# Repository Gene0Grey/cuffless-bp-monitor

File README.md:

# Cuffless BP Monitor

Cuffless, non-invasive blood-pressure monitoring using **Pulse Transit Time (PTT)**: one
AD8232 ECG gives the timing reference (the R-peak), and four MAX30102 PPG sensors on a
TCA9548A I²C multiplexer pick up the pulse wave at fingertips and earlobes. An ESP32
samples everything, filters it, and streams the waveforms.

This repository holds the carrier PCB (KiCad 9), the ESP32 firmware, and the
[project report](docs/Cuffless_BP_Monitor_Report.docx).

> **Not a medical device.** For research and education only; not validated for clinical use.

## How it works

Each heartbeat shows up as an R-peak on the ECG (t = 0). The pressure pulse it launches
reaches a peripheral site a short time later, where a PPG sensor sees it. That delay is the
PTT. Higher blood pressure stiffens the arteries, the pulse travels faster, and PTT gets
shorter:

```
BP ≈ a · (1 / PTT²) + b
```

`a` and `b` are fitted per person against a reference cuff. Using a proximal site
(earlobe, short PTT) and distal sites (fingertips, longer PTT) gives several transit times
per beat, for cross-checking and rejecting motion artefacts.

## System overview

The ECG is analog, so it goes straight to an ADC1 pin and keeps working with Wi-Fi on.
All four MAX30102 sensors share I²C address 0x57, so the TCA9548A connects one at a time.

## Hardware

### Carrier board

| | |
|---|---|
| Size | 95.5 × 76 mm, 4 × M3 holes |
| Copper | Single-sided (bottom), through-hole only, no vias. Built to be etched at home |
| Tracks | 0.5 mm signal, 0.8 mm power, ≥ 0.6 mm clearance, ground pour |
| Pads | 1.9 mm pads on 1.0 mm holes, sized for a hand drill |
| Power in | USB on the ESP32, or J1 (JST-PH 2-pin) → ESP32 VIN |

The four PPG sockets sit in one straight row, PPG1–PPG4 left to right on mux channels 0–3.
The bottom copper, seen from the component side:

### Renders

<table>
  <tr>
    <td></td>
    <td></td>
  </tr>
  <tr>
    <td align="center">Assembled, front right</td>
    <td align="center">Assembled, from the back: USB, 5V IN and the ECG jack</td>
  </tr>
  <tr>
    <td colspan="2"></td>
  </tr>
  <tr>
    <td colspan="2" align="center">The four PPG sockets, PPG1&ndash;PPG4 on mux channels 0&ndash;3</td>
  </tr>
  <tr>
    <td></td>
    <td></td>
  </tr>
  <tr>
    <td align="center">Bare board, top: silkscreen and pin names</td>
    <td align="center">Bare board, bottom: the single copper layer</td>
  </tr>
</table>

### Parts

| Ref | Part | Qty | Purpose |
|---|---|---|---|
| U1 | ESP32 DevKit V1, 30-pin (CP2102) | 1 | Acquisition, DSP, telemetry |
| U2 | TCA9548A I²C mux module (HW-617) | 1 | Addresses the four identical sensors |
| U3–U6 | MAX30102 module (MH-ET LIVE) | 4 | PPG: 2 fingers, 2 earlobes |
| U7 | SparkFun AD8232 (SEN-12650) + electrodes | 1 | ECG / R-peak reference |
| J1 | JST-PH 2-pin, vertical | 1 | 5 V input |
| C1 | 10 µF electrolytic | 1 | 3V3 bulk decoupling |
| JP1–JP5 | Bare-wire links | 5 | Jumpers for the single copper layer |

For portable use: a 3.7 V LiPo (1250 mAh) and an XL6009 boost converter set to 5.0 V, with
470 µF + 0.1 µF across both its input and its output. Full list:
[`hardware/docs/bom.csv`](hardware/docs/bom.csv).

### Pin map

| Module pin | ESP32 |
|---|---|
| TCA9548A VIN / GND | 3V3 / GND |
| TCA9548A SDA / SCL | GPIO21 / GPIO22 |
| TCA9548A A0, A1, A2 | GND (address 0x70) |
| TCA9548A RST | 3V3 (through link JP5) |
| MAX30102 #1 (finger) SDA / SCL | mux SD0 / SC0 |
| MAX30102 #2 (finger) SDA / SCL | mux SD1 / SC1 |
| MAX30102 #3 (earlobe) SDA / SCL | mux SD2 / SC2 |
| MAX30102 #4 (earlobe) SDA / SCL | mux SD3 / SC3 |
| AD8232 OUTPUT | GPIO34 (ADC1, works with Wi-Fi on) |
| AD8232 LO+ / LO− | GPIO32 / GPIO33 |
| AD8232 3.3V / GND | 3V3 / GND |
| AD8232 SDN, MAX30102 INT / RD / IRD | not connected |

All MAX30102 VIN pins go to 3V3 and all grounds are common. Electrodes: RA on the right
collarbone, LA on the left collarbone, RL (reference) on the left lower rib.

### Schematic

Click the image for the PDF.

### Assembly notes

- Fit the wire links first. JP1–JP4 join ground areas that the single layer splits apart,
  and JP5 carries 3V3 to the mux RST pin over the SDA/SCL tracks.
- Set the I²C level jumper on each MH-ET LIVE module to **3V3**.
- J1 pin 1 (rounded-square pad, by the **5V IN** label) takes 5 V. Pin 2 is GND. Feed it from the XL6009
  set to exactly 5.0 V. Check the voltage with a meter before connecting it.
- **Never power the board from USB and J1 at the same time.** Flash over USB first, then
  switch to battery.

## Firmware

[`firmware/cuffless_bp_monitor/cuffless_bp_monitor.ino`](firmware/cuffless_bp_monitor/cuffless_bp_monitor.ino)
is an Arduino sketch for the ESP32 core. The Wi-Fi dashboard needs two libraries,
listed under [Wi-Fi dashboard](#wi-fi-dashboard).

- Runs a 200 Hz processing loop and prints at 50 Hz over USB serial at 115200 baud. Each
  line is the ECG value followed by each detected PPG channel, tab-separated, so it works
  directly in the Arduino Serial Plotter.
- Finds sensors at start-up by part ID (0x15) and skips channels with no sensor.
- Selects the mux channel before each PPG read (ch0 = 0x01 … ch3 = 0x08).

| Stage | Technique | Removes |
|---|---|---|
| Hardware averaging | MAX30102 sample-average ×4 | Random sensor noise |
| Oversampling | 16× ADC average (ECG) | ADC jitter |
| Median | Median-of-3 (PPG) | Motion spikes |
| High-pass | Slow EMA baseline subtraction | Baseline wander, DC drift |
| Notch | 2nd-order IIR biquad (ECG) | Mains hum (`MAINS_HZ`, 50 or 60) |
| Low-pass | 2-pole cascaded EMA | High-frequency fuzz |
| Gain | Software gain + clamp | Scales the clean signal |

Tuning constants are grouped at the top of the sketch. Set `MAINS_HZ` to your local mains
frequency.

The USB serial output is unchanged by the dashboard, so the Serial Plotter still works.

## Wi-Fi dashboard

The ESP32 serves its own dashboard. Open it in any browser on the same network to see
the ECG and all four PPG sites live, with:

- heart rate from the ECG R-peaks;
- pulse transit time per site, in ms (raw, uncalibrated, and never a blood-pressure value);
- a status for every channel: leads off, no sensor, no contact, clipping;
- **Record**, which saves the session as a CSV file when you stop.

Nothing needs installing on the viewing side, and it works without internet.

<table>
  <tr>
    <td width="70%"></td>
    <td width="30%"></td>
  </tr>
  <tr>
    <td align="center">Dark mode follows the system setting</td>
    <td align="center">On a phone</td>
  </tr>
</table>

When a channel has a problem, the status row and the channel itself say what to fix:

### Setting it up

1. In the Arduino IDE Library Manager, install **ESP Async WebServer** and **AsyncTCP**
   (both by ESP32Async).
2. Copy `firmware/cuffless_bp_monitor/wifi_secrets.example.h` to `wifi_secrets.h` in the
   same folder and enter your Wi-Fi name and password. Optionally set a fixed IP address.
   `wifi_secrets.h` is git-ignored, so the password stays on your computer.
3. Flash the sketch and open the Serial Monitor at 115200 baud. The board prints the
   dashboard address, for example `Dashboard: http://192.168.1.50`. It also answers at
   `http://cuffless-bp.local` on most laptops.

If the board can't join your Wi-Fi within 10 seconds, or there is no `wifi_secrets.h`, it
opens its own hotspot instead: `CufflessBP-XXXX`, password `cuffless-bp`, dashboard at
`http://192.168.4.1`. Change that password with `HOTSPOT_PASS` in `wifi_secrets.h`.

Add `?demo` to the address to see the dashboard with synthetic data. The page labels it
clearly as demo data.

### Recordings

Each CSV has one row per ECG sample (200 Hz), with the four PPG columns filled every
fourth row (50 Hz):

```
t_s,ecg,leads_off,ppg1_ch0,ppg2_ch1,ppg3_ch2,ppg4_ch3
```

Values are exactly what the board sends: the filtered ECG, and the filtered PPG infrared
channel, not inverted. A PPG column is left empty when that sensor isn't detected.

### Editing the page

The page source is `firmware/cuffless_bp_monitor/dashboard/index.html`. After changing
it, run `python embed.py` in that folder. This regenerates `dashboard_page.h`, the
compressed copy that gets compiled into the firmware.

## Repository layout

```
hardware/              KiCad 9 project (ppg-ecg-carrier)
  lib/                 footprints, symbols, logo
  fab/                 Gerbers + Excellon drill file
  docs/                schematic, etch / assembly / drill PDFs, BOM
firmware/              ESP32 Arduino sketch
  cuffless_bp_monitor/dashboard/   Wi-Fi dashboard page
docs/                  project report
  images/              renders, diagrams, dashboard screenshots
```

## Opening the design

Open `hardware/ppg-ecg-carrier.kicad_pro` in KiCad 9. The footprints and symbols for
the four modules are in the project's own library (`hardware/lib/`), so nothing else
needs installing.

### 3D models

The STEP models of the four modules are third-party files and are not included. To see
them in KiCad's 3D viewer, put these files in `hardware/lib/3d/`:

- `esp32_30pin.step`
- `TCA9548.stp`
- `MAX30102_MH_ET_LIVE_BOARD_v8.step`
- `AD8232_Heart_Rate_Monitor v4.step`

## Fabrication

- **Home etching:** print [`hardware/docs/etch-bottom.pdf`](hardware/docs/etch-bottom.pdf)
  at 100 % scale. It is already mirrored for toner transfer.
- **Drilling:** [`drill-map.pdf`](hardware/docs/drill-map.pdf) shows the holes. Fit the
  parts using [`assembly-top.pdf`](hardware/docs/assembly-top.pdf).
- **Fab house:** upload [`hardware/fab/`](hardware/fab) as a 2-layer board. The top-copper
  Gerber holds only the five wire links, drawn as tracks, so a fabbed board needs no
  wire links.

## Limitations

- PTT-based BP needs per-person calibration against a cuff and drifts over time. Treat it
  as a trend monitor.
- The PPG sensors are read one at a time through the mux, so their timing has to be
  reconstructed in software.
- The ESP32's internal ADC is noisy. Oversampling helps, but an external ADC would give a
  cleaner ECG.
- Both signals are sensitive to motion and to poor electrode or sensor contact.

## Roadmap

1. R-peak detection on the ECG (Pan–Tompkins-style thresholding)
2. Pulse-foot detection on each PPG channel
3. PTT per site and per beat: t(PPG foot) − t(ECG R-peak)
4. Calibration against a reference cuff to fit `a` and `b`
5. On-device BP calculation, transmitting only the result
6. OTA updates and a wearable enclosure

## Author

**Sahil Krishna N** ([@Gene0Grey](https://github.com/Gene0Grey))

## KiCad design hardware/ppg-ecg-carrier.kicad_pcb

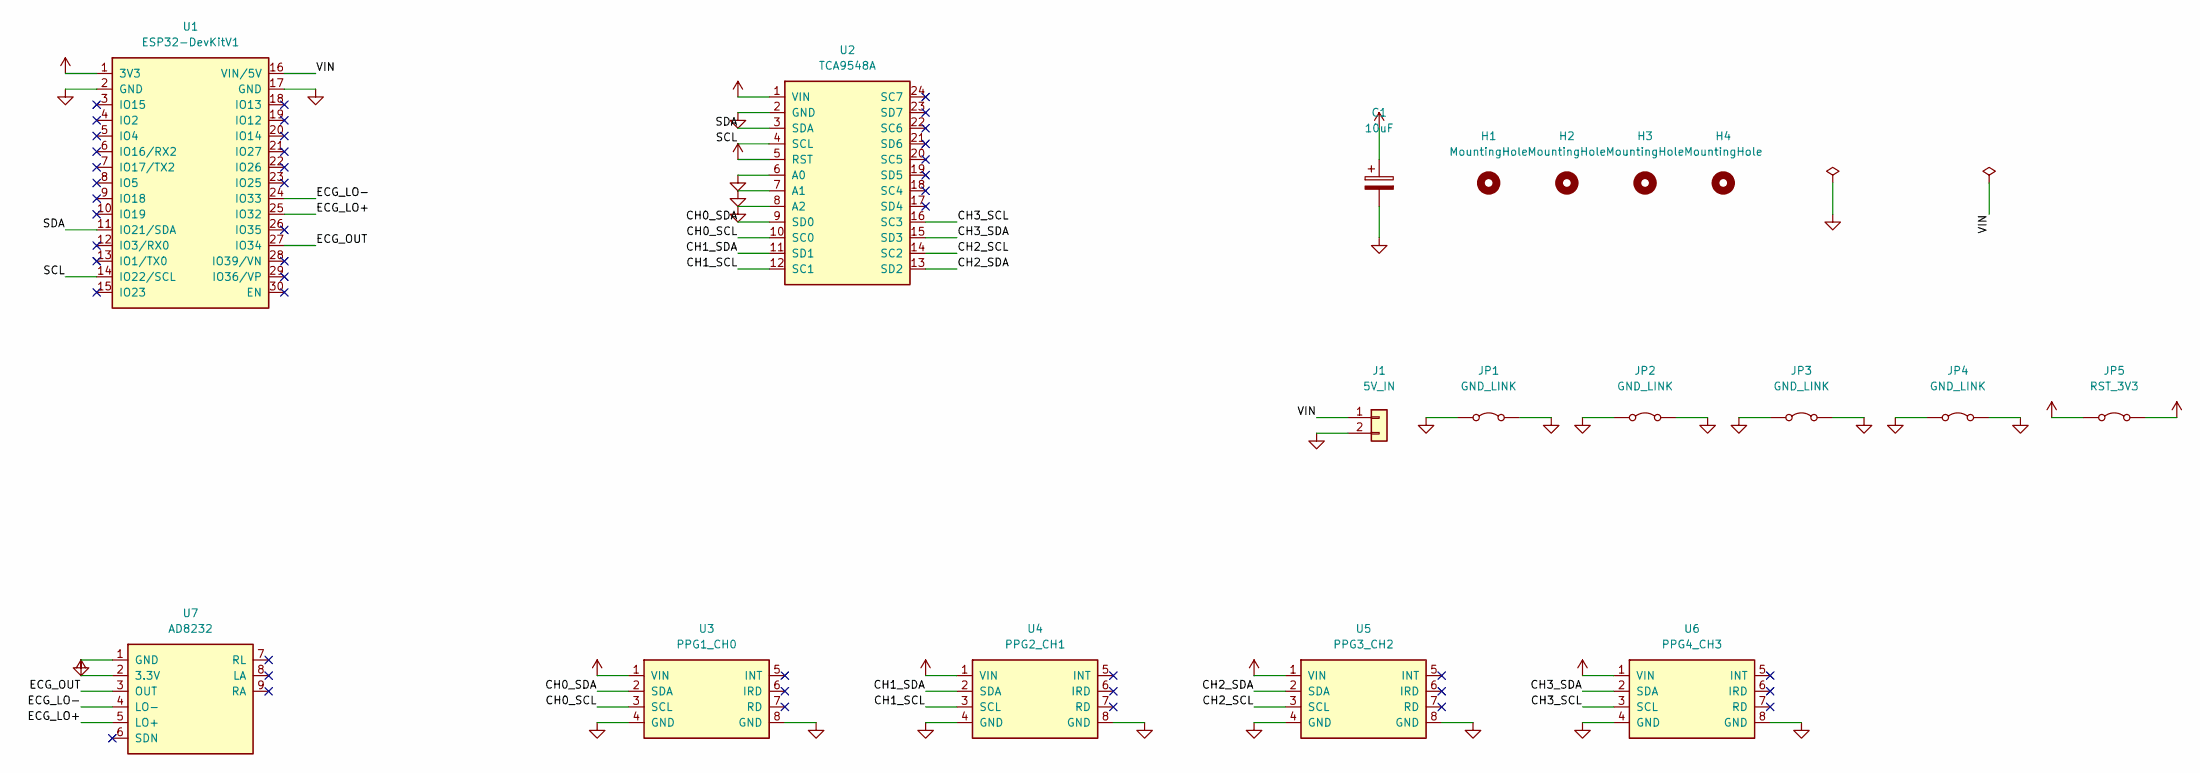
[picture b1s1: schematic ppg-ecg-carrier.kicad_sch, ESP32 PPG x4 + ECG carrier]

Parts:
C1: 10uF; CP_Radial_D5.0mm_P2.50mm
H1, H2, H3, H4: MountingHole; MountingHole_3.2mm_M3
J1: 5V_IN; JST_PH_B2B-PH-K_1x02_P2.00mm_Vertical_HandDrill
JP1, JP2, JP3, JP4: GND_LINK; WireLink_P5.08mm
JP5: RST_3V3; WireLink_P5.08mm
U1: ESP32-DevKitV1; ESP32_DevKitV1_30pin
U2: TCA9548A; TCA9548A_Module_HW-617
U3: PPG1_CH0; MAX30102_MH-ET_LIVE
U4: PPG2_CH1; MAX30102_MH-ET_LIVE
U5: PPG3_CH2; MAX30102_MH-ET_LIVE
U6: PPG4_CH3; MAX30102_MH-ET_LIVE
U7: AD8232; AD8232_SparkFun_SEN-12650

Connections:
+3V3: C1.1, JP5.1 (A), JP5.2 (B), U1.1 (3V3), U2.1 (VIN), U2.5 (RST), U3.1 (VIN), U4.1 (VIN), U5.1 (VIN), U6.1 (VIN), U7.2 (3.3V)
/CH0_SCL: U2.10 (SC0), U3.3 (SCL)
/CH0_SDA: U2.9 (SD0), U3.2 (SDA)
/CH1_SCL: U2.12 (SC1), U4.3 (SCL)
/CH1_SDA: U2.11 (SD1), U4.2 (SDA)
/CH2_SCL: U2.14 (SC2), U5.3 (SCL)
/CH2_SDA: U2.13 (SD2), U5.2 (SDA)
/CH3_SCL: U2.16 (SC3), U6.3 (SCL)
/CH3_SDA: U2.15 (SD3), U6.2 (SDA)
/ECG_LO+: U1.25 (IO32), U7.5 (LO+)
/ECG_LO-: U1.24 (IO33), U7.4 (LO-)
/ECG_OUT: U1.27 (IO34), U7.3 (OUT)
/SCL: U1.14 (IO22/SCL), U2.4 (SCL)
/SDA: U1.11 (IO21/SDA), U2.3 (SDA)
/VIN: J1.1, U1.16 (VIN/5V)
GND: C1.2, J1.2, JP1.1 (A), JP1.2 (B), JP2.1 (A), JP2.2 (B), JP3.1 (A), JP3.2 (B), JP4.1 (A), JP4.2 (B), U1.2 (GND), U1.17 (GND), U2.2 (GND), U2.6 (A0), U2.7 (A1), U2.8 (A2), U3.4 (GND), U3.8 (GND), U4.4 (GND), U4.8 (GND), U5.4 (GND), U5.8 (GND), U6.4 (GND), U6.8 (GND), U7.1 (GND)

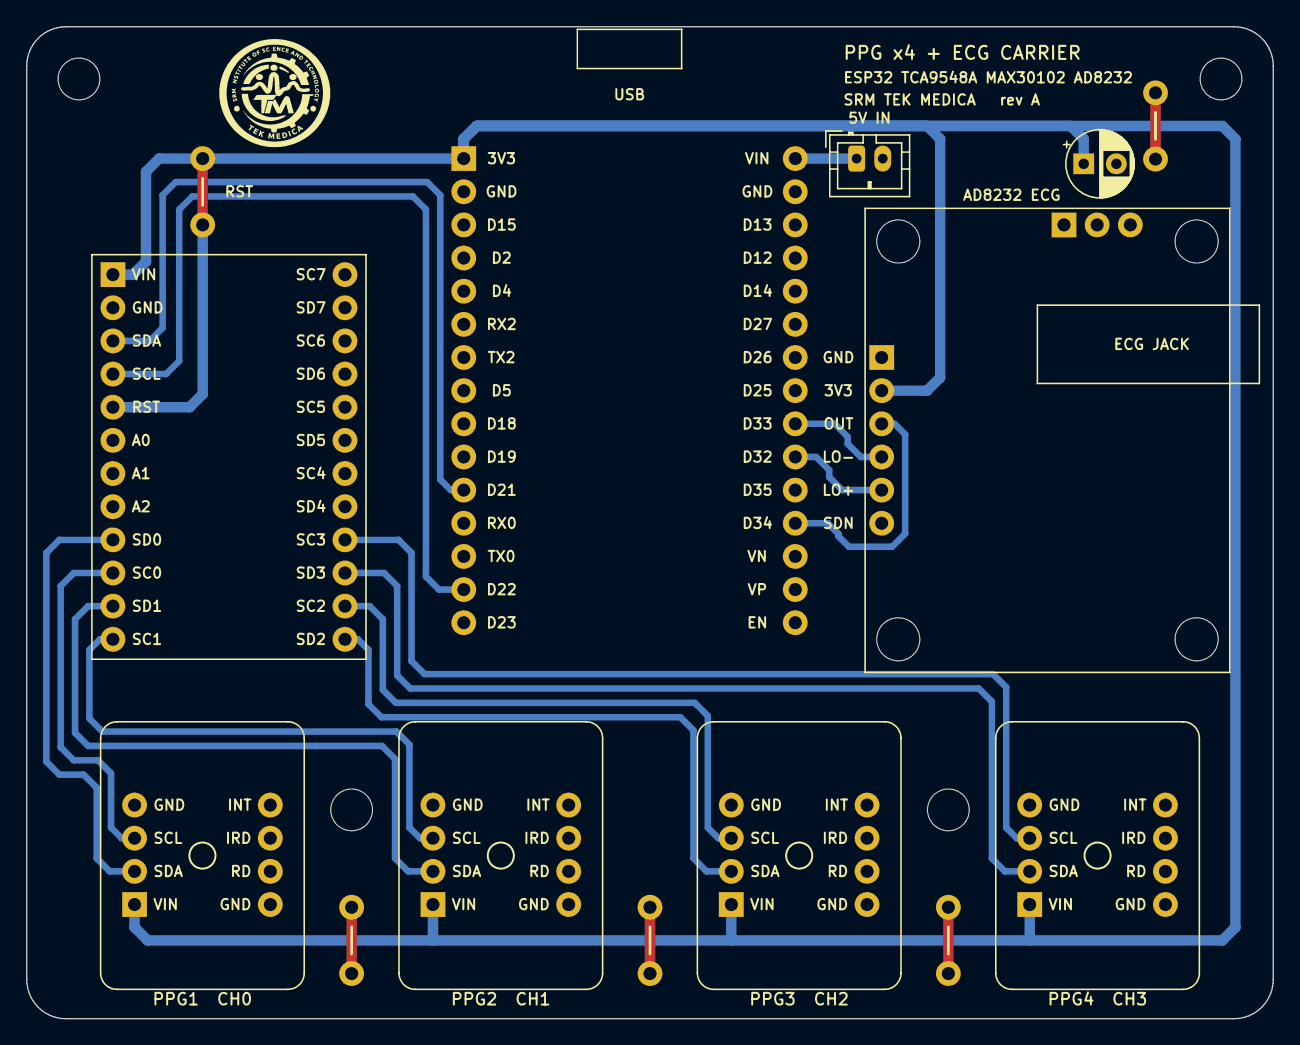
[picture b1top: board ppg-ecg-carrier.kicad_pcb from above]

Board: 2 copper layers, 95.5 x 76.0 mm, 18 parts (0 on the bottom side), 16 nets.

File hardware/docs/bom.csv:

"Reference","Value","Footprint","QUANTITY"
"C1","10uF","Capacitor_THT:CP_Radial_D5.0mm_P2.50mm","1"
"H1-H4","MountingHole","MountingHole:MountingHole_3.2mm_M3","4"
"J1","5V_IN","ppg:JST_PH_B2B-PH-K_1x02_P2.00mm_Vertical_HandDrill","1"
"JP1-JP4","GND_LINK","ppg:WireLink_P5.08mm","4"
"JP5","RST_3V3","ppg:WireLink_P5.08mm","1"
"U1","ESP32-DevKitV1","ppg:ESP32_DevKitV1_30pin","1"
"U2","TCA9548A","ppg:TCA9548A_Module_HW-617","1"
"U3","PPG1_CH0","ppg:MAX30102_MH-ET_LIVE","1"
"U4","PPG2_CH1","ppg:MAX30102_MH-ET_LIVE","1"
"U5","PPG3_CH2","ppg:MAX30102_MH-ET_LIVE","1"
"U6","PPG4_CH3","ppg:MAX30102_MH-ET_LIVE","1"
"U7","AD8232","ppg:AD8232_SparkFun_SEN-12650","1"
